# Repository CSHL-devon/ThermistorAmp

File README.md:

# Thermistor Amplifier

A thermistor amplifier for capturing sniff signals in rodents

## General Use

The circuit takes +5V DC and converts to +/-5V DC for the amp. Using the bias trimmer, you can roughly zero the input from the thermistor, allowing +/-5V swings depending on which side of the sniff you're on. I say roughly because the temperature is never static, so the baseline will drift up and down over the experiment. I considered using a chopper amp to pin the baseline to zero, but there's too much signal loss.  

The Gain trimmer will adjust the level of amplification. The range is not huge, but some thermistor implantations run hotter than others, so it's nice to have a bit of flexibility.

The thermistor gets connected to the 3-position screw terminal. "+5V" is going out from the board into the thermistor, while "In" is the input from the thermistor to the amp. The third position is connected to ground so you can connect cable shielding, which is techinally optional, but very highly recommended.

## Building

UPDATE: By popular demand, this is now made exclusively with through-hole parts, so building is trivial.

### Build Order

- Resistors
- IC Socket
- Capacitors
- Inductor
- Screw Terminals
- DCDC Converter
- Trimmers

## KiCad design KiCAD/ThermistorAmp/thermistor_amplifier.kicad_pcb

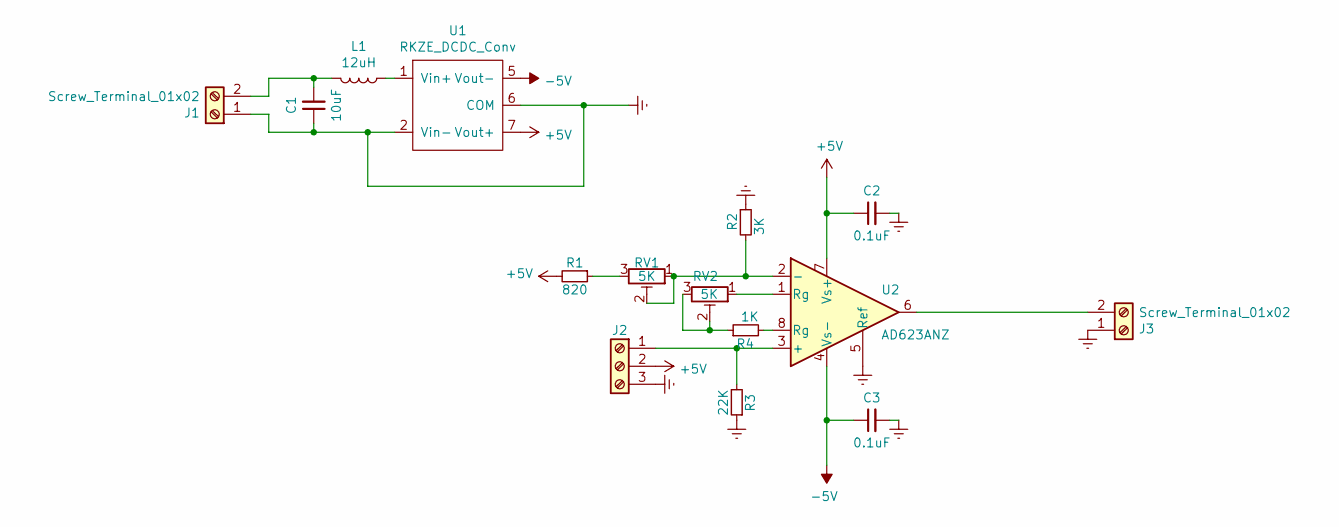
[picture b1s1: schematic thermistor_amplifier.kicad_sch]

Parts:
C1: 10uF; C_Disc_D5.0mm_W2.5mm_P2.50mm
C2, C3: 0.1uF; C_Disc_D5.0mm_W2.5mm_P2.50mm
J1, J3: Screw_Terminal_01x02; TerminalBlock_Phoenix_MPT-0,5-2-2.54_1x02_P2.54mm_Horizontal
J2: Screw_Terminal_01x03; TerminalBlock_Phoenix_MPT-0,5-3-2.54_1x03_P2.54mm_Horizontal
L1: 12uH; C_Radial_D5.0mm_H7.0mm_P2.00mm
R1: 820; R_Axial_DIN0207_L6.3mm_D2.5mm_P10.16mm_Horizontal
R2: 3K; R_Axial_DIN0207_L6.3mm_D2.5mm_P10.16mm_Horizontal
R3: 22K; R_Axial_DIN0207_L6.3mm_D2.5mm_P10.16mm_Horizontal
R4: 1K; R_Axial_DIN0207_L6.3mm_D2.5mm_P10.16mm_Horizontal
RV1, RV2: 5K; Potentiometer_Bourns_3386P_Vertical
U1: RKZE_DCDC_Conv
U2: AD623ANZ; DIP-8_W7.62mm

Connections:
+5V: C2.1, J2.2, R1.2, U1.7 (Vout+), U2.7 (Vs+)
-5V: C3.1, U1.5 (Vout-), U2.4 (Vs-)
Earth: C1.1, C2.2, C3.2, J1.1, J2.3, J3.1, R2.1, R3.1, U1.2 (Vin-), U1.6 (COM), U2.5 (Ref)
unnamed: C1.2, J1.2, L1.2
unnamed: J2.1, R3.2, U2.3 (+)
unnamed: J3.2, U2.6
unnamed: L1.1, U1.1 (Vin+)
unnamed: R1.1, RV1.3
unnamed: R2.2, RV1.1, RV1.2, U2.2 (-)
unnamed: R4.1, RV2.2, RV2.3
unnamed: R4.2, U2.8 (Rg)
unnamed: RV2.1, U2.1 (Rg)

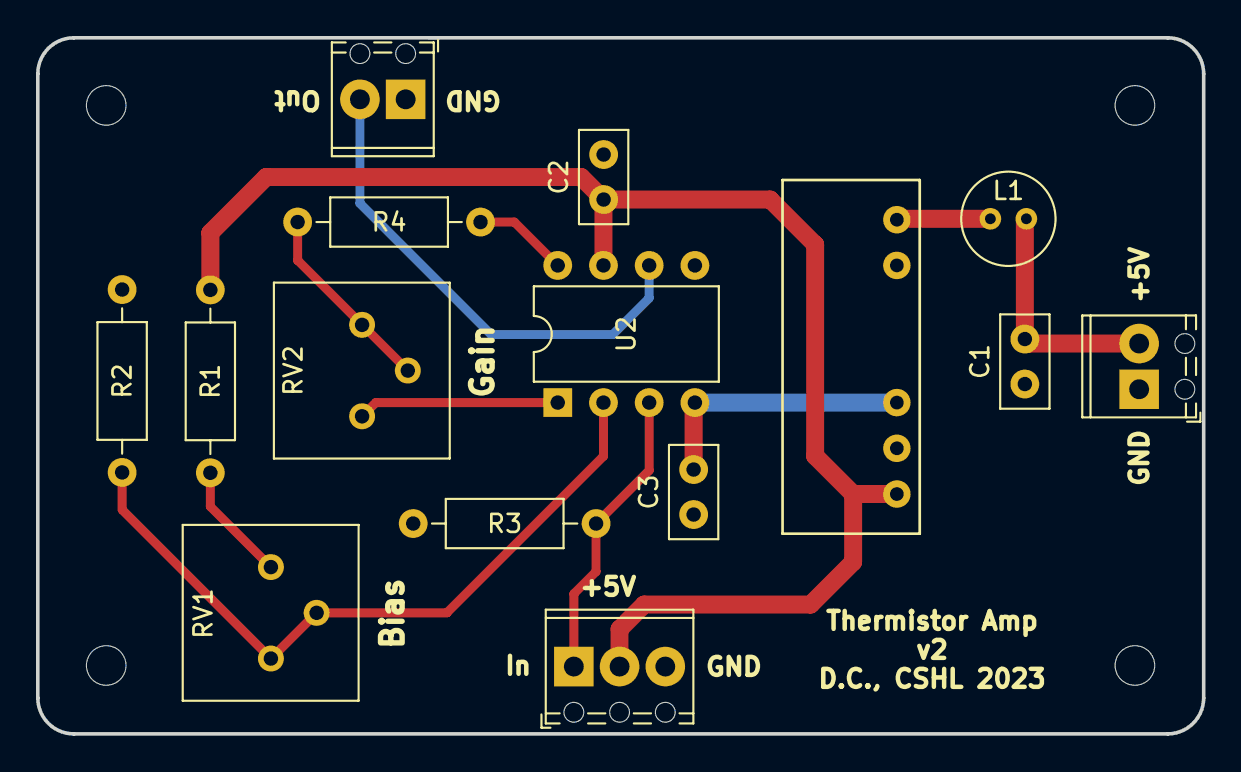
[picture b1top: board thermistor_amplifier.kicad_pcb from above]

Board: 2 copper layers, 64.8 x 38.7 mm, 15 parts (0 on the bottom side), 12 nets.

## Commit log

2023-03-28 Formatting
2023-03-28 Add schematic image
2023-05-15 Update thermistor amp to V2
2023-11-08 New Part# for Inst Amp
2024-03-14 Update image
2024-03-14 Correction
2024-03-14 Backups
